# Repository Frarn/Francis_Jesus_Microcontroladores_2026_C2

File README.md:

# Francis_Jesus_Microcontroladores_2026_C2

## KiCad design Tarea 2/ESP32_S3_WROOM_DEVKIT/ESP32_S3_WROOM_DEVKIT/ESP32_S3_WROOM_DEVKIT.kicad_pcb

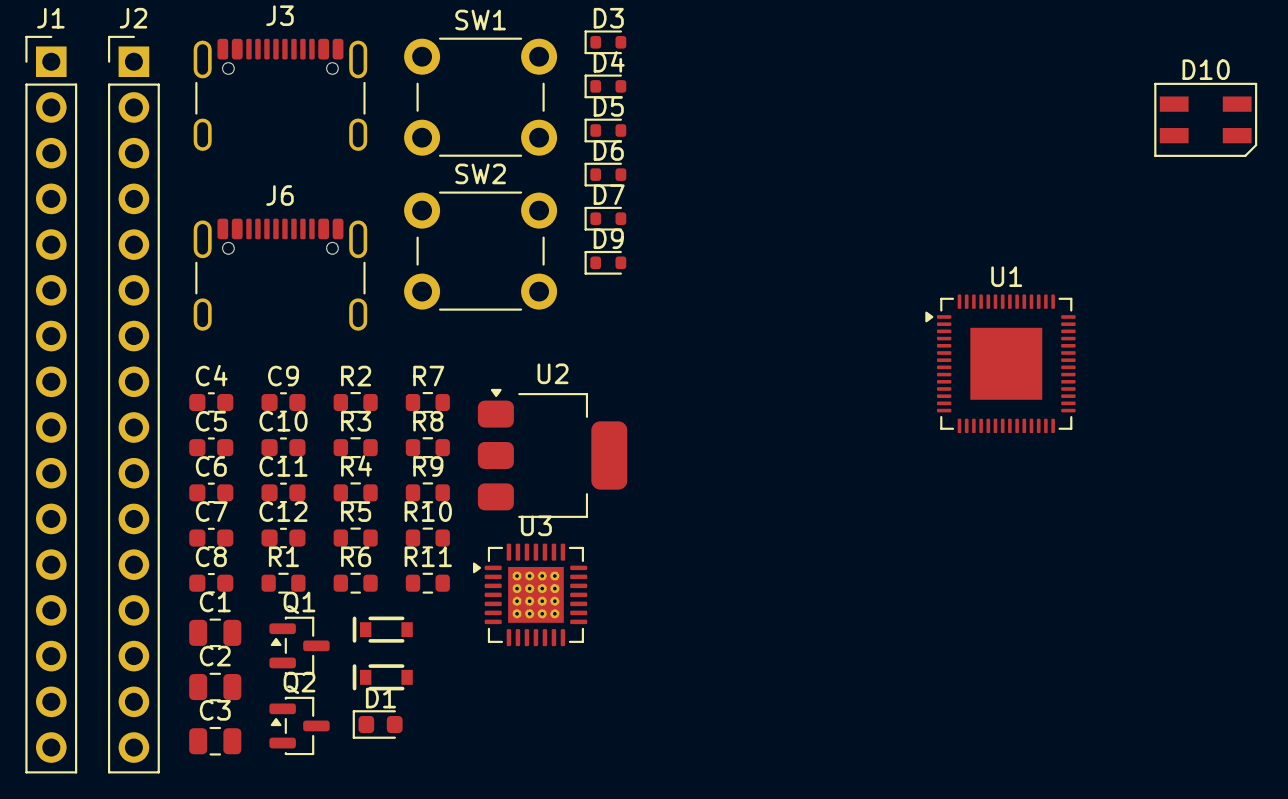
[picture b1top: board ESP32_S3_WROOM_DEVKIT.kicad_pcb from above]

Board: 2 copper layers, 44 parts (0 on the bottom side), 30 nets, no tracks yet.

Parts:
C1, C2, C3: C45783; C_0805_2012Metric
C4, C5, C6, C7, C9, C12: C14663; C_0603_1608Metric
C8, C10, C11: C96446; C_0603_1608Metric
D1: C2286; LED_0603_1608Metric
D2, D8: C82544; SOD-323
D3, D4, D5, D6, D7, D9: C5199850; D_SOD-523
D10: C7423117; LED_SK6812MINI_PLCC4_3.5x3.5mm_P1.75mm
J1, J2: Conn_01x22_Socket; PinHeader_1x16_P2.54mm_Vertical
J3, J6: C165948; USB_C_Receptacle_GCT_USB4105-xx-A_16P_TopMnt_Horizontal
Q1, Q2: C49581; SOT-23
R1, R9: C22975; R_0603_1608Metric
R2, R5, R6: C25804; R_0603_1608Metric
R3, R4, R11: C21189; R_0603_1608Metric
R7: C31850; R_0603_1608Metric
R8: C25819; R_0603_1608Metric
R10: 10K DNP; R_0603_1608Metric
SW1, SW2: SW_Push; SW_PUSH_6mm
U1: ESP32-S3; QFN-56-1EP_7x7mm_P0.4mm_EP4x4mm
U2: C6186; SOT-223-3_TabPin2
U3: C964632; QFN-28-1EP_5x5mm_P0.5mm_EP3.1x3.1mm_ThermalVias

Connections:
3.3V: C2.1, C3.1, C4.1, C8.1, C9.1, D10.4 (VDD), J2.1, J2.2, R2.1, R9.1, U2.2 (VO), U3.6 (VDD), U3.7 (VREGIN)
5V: C1.1, C10.1, C11.1, D2.1 (K), D8.1 (K), R1.1, U2.3 (VI)
/DN: D4.2 (A2), J6.A7 (D-), J6.B7 (D-), U3.5 (D-)
/DP: D5.2 (A2), J6.A6 (D+), J6.B6 (D+), U3.4 (D+)
/DTR: Q2.3 (C), R5.1, U3.28 (~DTR)
/EN: C5.1, C6.2, J2.3, Q1.3 (C), R2.2, SW1.2
/GPIO19: D9.2 (A2), J3.A6 (D+), J3.B6 (D+)
/GPIO20: D7.2 (A2), J3.A7 (D-), J3.B7 (D-)
/GPIO38: J1.10, R11.2
/GPIO39: J1.9, U1.44 (MTCK)
/GPIO40: J1.8, U1.45 (MTDO)
/GPIO41: J1.7, U1.47 (MTDI)
/GPIO42: J1.6, U1.48 (MTMS)
/IO0: C7.2, Q2.2 (E), SW2.2
/RGB_CONTROL: D10.3 (DIN), R11.1
/RTS: Q1.2 (E), R6.1, U3.24 (~RTS)
/RXD: R3.1, U3.25 (RXD)
/TXD: R4.1, U3.26 (TXD)
/U0RXDO: J1.3, R4.2
/U0TXDO: J1.2, R3.2
/VBUS: D2.2 (A), D3.2 (A2), D6.2 (A2), D8.2 (A), J3.A4 (VBUS), J3.A9 (VBUS), J3.B4 (VBUS), J3.B9 (VBUS), J6.A4 (VBUS), J6.A9 (VBUS), J6.B4 (VBUS), J6.B9 (VBUS), R7.1
GND: C1.2, C2.2, C3.2, C4.2, C5.2, C6.1, C7.1, C8.2, C9.2, C10.2, C11.2, C12.2, D1.1 (K), D3.1 (A1), D4.1 (A1), D5.1 (A1), D6.1 (A1), D7.1 (A1), D9.1 (A1), D10.2 (VSS), J1.1, J3.A1 (GND), J3.A12 (GND), J3.B1 (GND), J3.B12 (GND), J3.S1 (SHIELD), J6.A1 (GND), J6.A12 (GND), J6.B1 (GND), J6.B12 (GND), J6.S1 (SHIELD), R8.1, R10.2, SW1.1, SW2.1, U1.57 (GND), U2.1 (GND), U3.3 (GND), U3.29 (GND)
unnamed: D1.2 (A), R1.2
unnamed: Q1.1 (B), R5.2
unnamed: Q2.1 (B), R6.2
unnamed: U1.2 (VDD3P3), U1.3 (VDD3P3)
unnamed: U1.55 (VDDA), U1.56 (VDDA)
unnamed: C12.1, R7.2, R8.2, U3.8 (VBUS)
unnamed: R9.2, U3.9 (~RST)
unnamed: R10.1, U3.11 (~SUSPEND)

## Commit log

2026-06-11 Create Tarea 2
